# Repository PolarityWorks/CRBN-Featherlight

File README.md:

# CRBN-Featherlight

<br />The CRBN Featherlight is licensed under a <a rel="license" href="http://creativecommons.org/licenses/by-nc-sa/4.0/">Creative Commons Attribution-NonCommercial-ShareAlike 4.0 International License</a>.

The PCB and case design may be freely reproduced, modified, and manufactured for personal use and may not be reproduced for public sale.

If you have built upon this work please contact us at polarity.works.1@gmail.com. We fully support those looking to make new things and will most likely support your project.

[Build Guide](https://drive.google.com/file/d/1sr51WLZUvYGmcUbsTRLLeZIsZQXj4blm/view)

[Kits are sold here](https://keygem.store/collections/keyboards/products/group-buy-featherlight-40-kit)

[QMK Firmware](https://config.qmk.fm/#/crbn/LAYOUT_crbn_1x2u)

[ZMK Firmware](https://github.com/zmkfirmware/zmk/tree/main)

This little 40% ortho punches well above its weight and its price tag. Tough enough to survive life on the go or beating down someone that disses it.
It's got all the configuration options you'd ever want in a 40%. All the components are through-hole so it's a great first keyboard kit to put togethether.
You will need a pro micro for the PCB which gives you lots of options for extra features. You can solder in an elite c to get USB C or even a nice nano to make it wireless! There's plenty of room between the PCB and the bottom plate for a huge lithium battery.
This would be a vicious travel keyboard, a macro pad for productivity people, the first ortho for people who want to try ortho, or just a cute little keyboard to lend to people when they need one.

## Specifications
* Only 300g
* Stacked carbon fiber switch plate and bottom
* Supoport for a rotary encoder - this can be place in one of the corners
* Sevral bottom row layouts
* QMK and ZMK support

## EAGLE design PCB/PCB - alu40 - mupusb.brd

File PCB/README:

Components Needed:
1N4148 DO-35 Diodes               x48
6x6mm tactile button              x1
12x1 pin header 2.54mm pitch      x2
Pro Micro Compatible or Nice Nano x1
Key Switches                      x44-48

Optional:
EC11 Rotary Encoder               x1
Stabilisers (2u or 4u)            x1-2

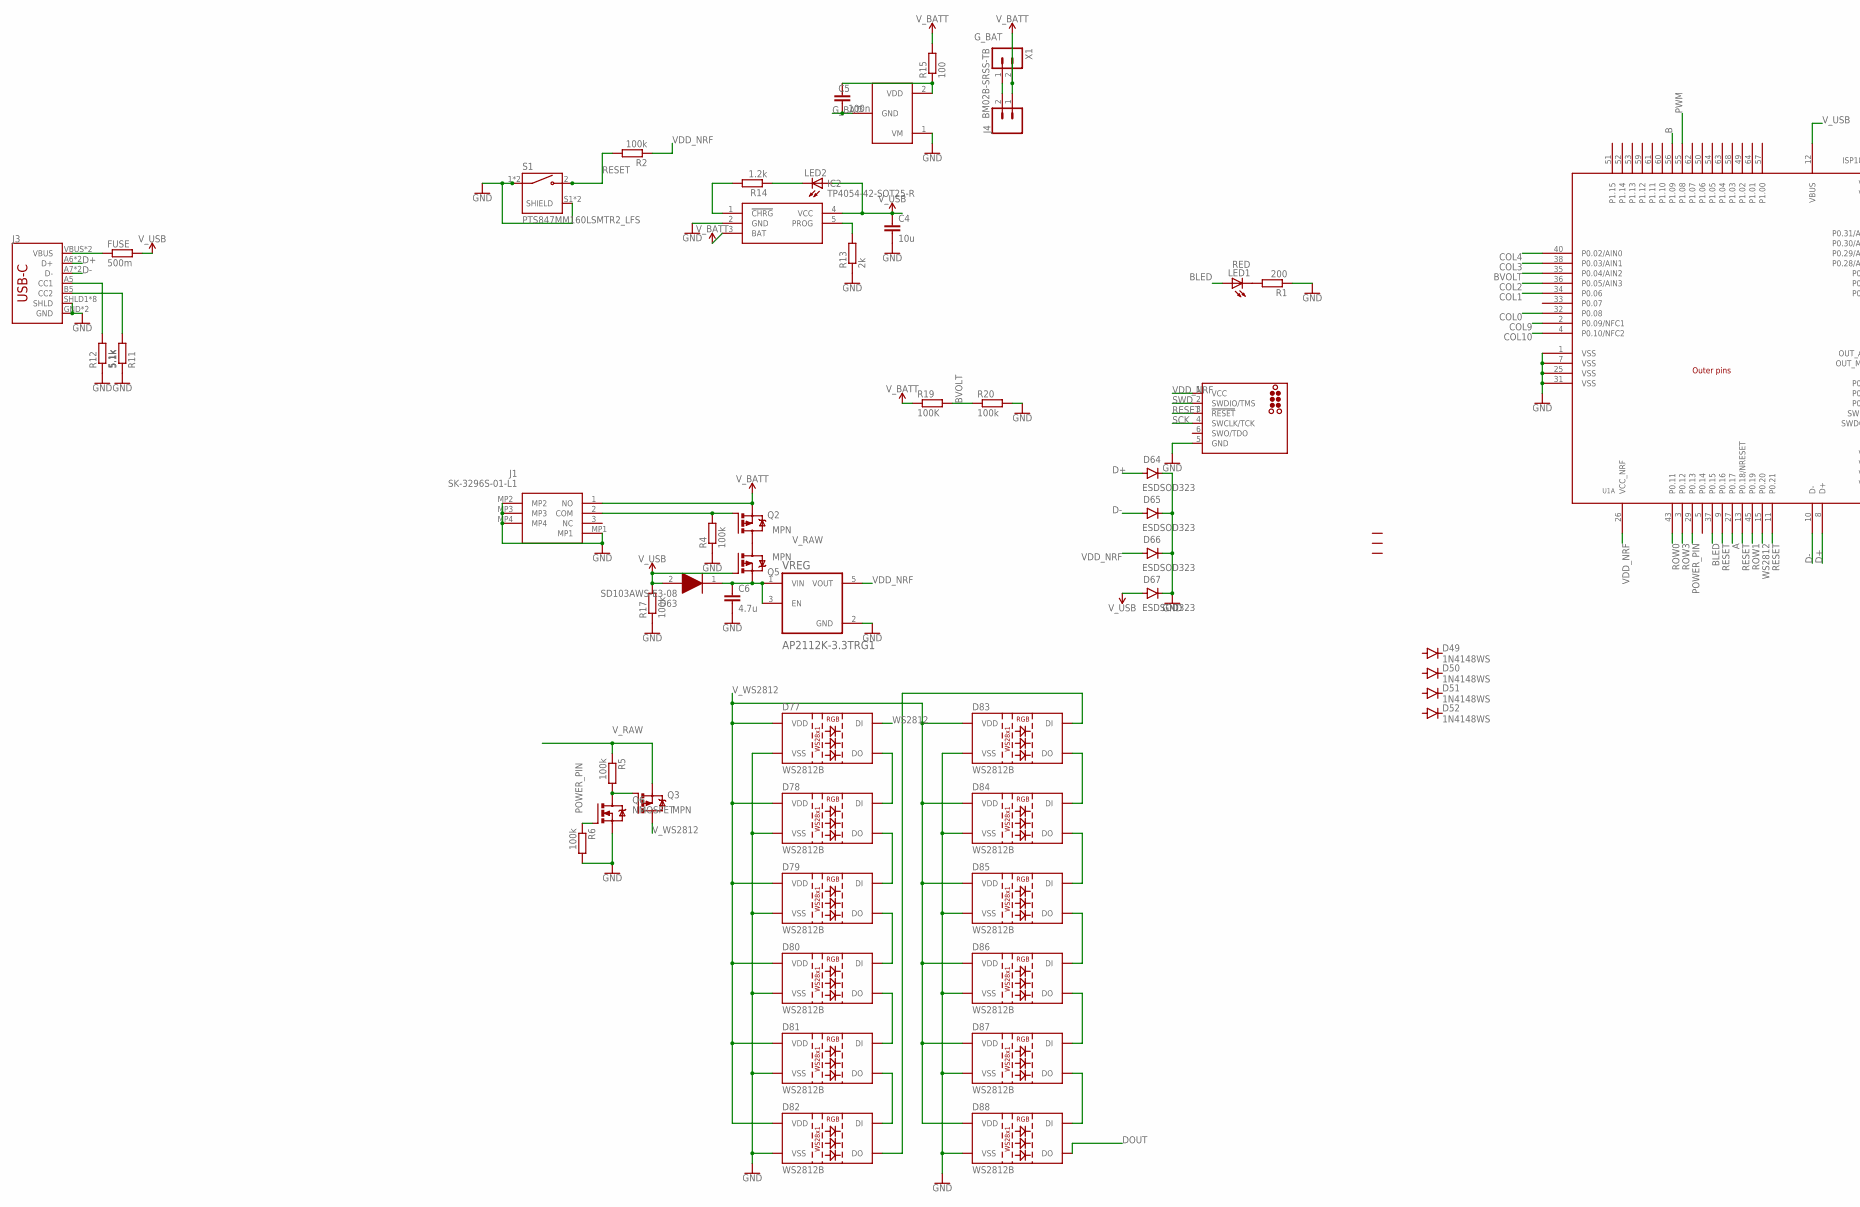
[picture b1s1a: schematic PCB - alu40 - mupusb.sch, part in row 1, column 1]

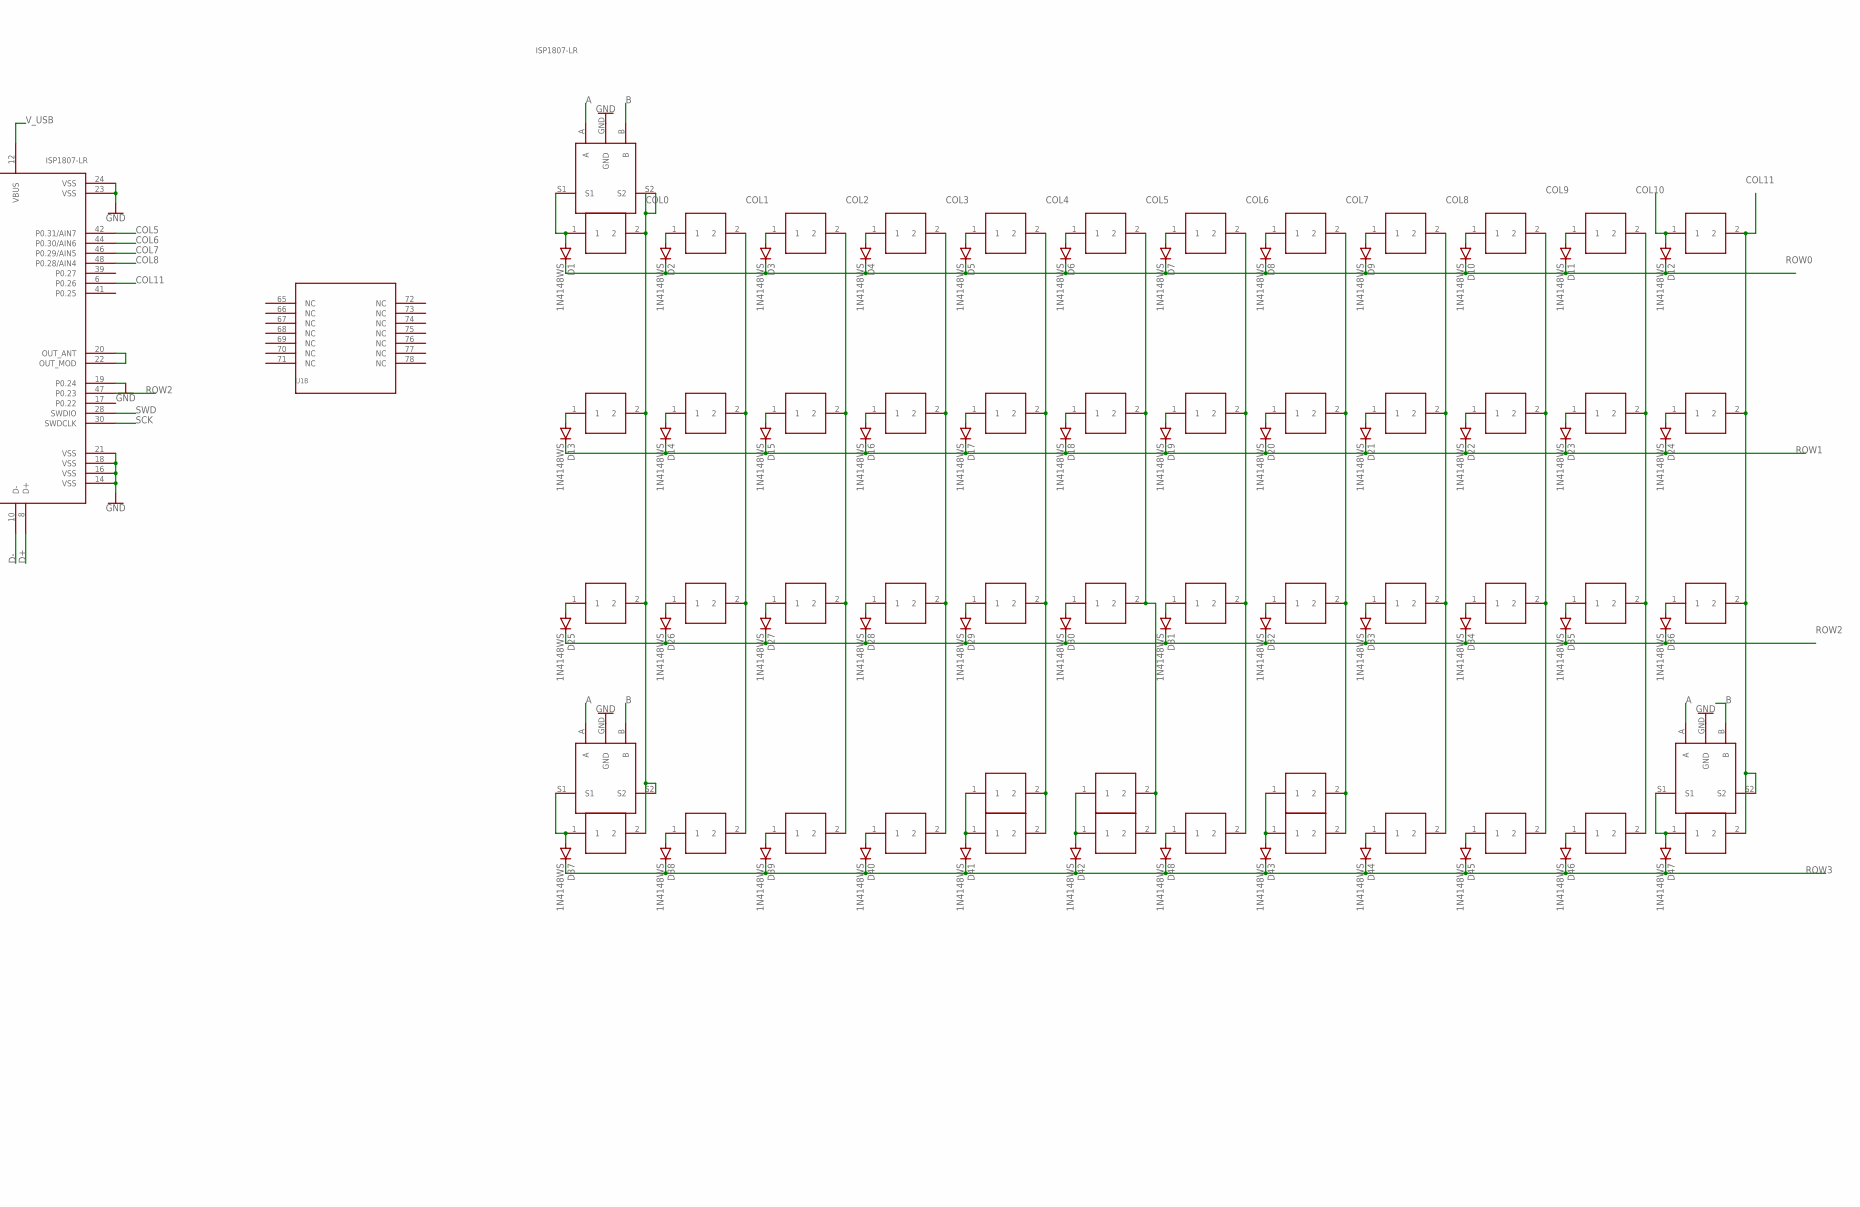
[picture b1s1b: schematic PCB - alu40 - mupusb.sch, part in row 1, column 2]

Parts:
11, 12, 13, 14, 15, 16, 17, 18, 19, 21, 22, 23, 24, 25, 26, 27, 28, 29, 31, 32, 33, 34, 35, 36, 37, 38, 39, 41, 42, 43, 44, 45, 45-2, 46, 46-2, 47, 48, 48-2, 49, 110, 111, 112, 210, 211, 212, 310, 311, 312, 410, 411, 412: CHERRY
11ENC, 41ENC\, 412ENC: ENCODERHOLE; ENCODER
C4: 10u; C0603
C5: 100n; C0603
C6: 4.7u; C0603
D1, D2, D3, D4, D5, D6, D7, D8, D9, D10, D11, D12, D13, D14, D15, D16, D17, D18, D19, D20, D21, D22, D23, D24, D25, D26, D27, D28, D29, D30, D31, D32, D33, D34, D35, D36, D37, D38, D39, D40, D41, D42, D43, D44, D45, D46, D47, D48, D49, D50, D51, D52: 1N4148WS; SOD-323
D63: SD103AWS-E3-08; SOD2713X115N
D64, D65, D66, D67: ESDSOD323; SOD-323
D77, D78, D79, D80, D81, D82, D83, D84, D85, D86, D87, D88: WS2812B
FUSE: 500m; R0603
IC1: XB3303ASOT23; SOT23-3
IC2: TP4054-42-SOT25-R; SOT95P280X100-5N
J1: SK-3296S-01-L1; SK3296S01L1
J2: TC2030_SWD-MCP-NL; TC2030-MCP-NL
J3: SPARKFUN-CONNECTORS_USB_C; MUP-MIDMNT-SS
J4: CONN_02; 1X02
LED1: RED; CHIPLED_0805
LED2: LEDCHIPLED_0805; CHIPLED_0805
Q2, Q3, Q5: PMOSFET; SOT23; MPN SL2301S
Q6: NMOSFET; SOT23
R1: 200; R0603
R2, R4, R5, R6, R17, R20: 100k; R0603
R11, R12: 5.1k; R0603
R13: 2k; R0603
R14: 1.2k; R0603
R15: 100; R0603
R19: 100K; R0603
S1: PTS847MM160LSMTR2_LFS; SW_PTS847MM160LSMTR2_LFS
U1: ISP1807-LRISP1807-LR_ISP1807-LR; ISP1807-LR
U$8, U$9, U$10: STAB-2U
VREG: AP2112K-3.3TRG1; SOT95P285X140-5N
X1: BM02B-SRSS-TB

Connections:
A: 11ENC.A, 41ENC\.A, 412ENC.A, U1.27 (P0.17)
B: 11ENC.B, 41ENC\.B, 412ENC.B, U1.56 (P1.09)
BLED: LED1.A, U1.37 (P0.15)
BVOLT: R19.2, R20.1, U1.35 (P0.04/AIN2)
COL0: 11.2, 11ENC.S2, 21.2, 31.2, 41.2, 41ENC\.S2, U1.32 (P0.08)
COL1: 12.2, 22.2, 32.2, 42.2, U1.34 (P0.06)
COL2: 13.2, 23.2, 33.2, 43.2, U1.36 (P0.05/AIN3)
COL3: 14.2, 24.2, 34.2, 44.2, U1.38 (P0.03/AIN1)
COL4: 15.2, 25.2, 35.2, 45.2, 45-2.2, U1.40 (P0.02/AIN0)
COL5: 16.2, 26.2, 36.2, 46.2, 46-2.2, U1.42 (P0.31/AIN7)
COL6: 17.2, 27.2, 37.2, 47.2, U1.44 (P0.30/AIN6)
COL7: 18.2, 28.2, 38.2, 48.2, 48-2.2, U1.46 (P0.29/AIN5)
COL8: 19.2, 29.2, 39.2, 49.2, U1.48 (P0.28/AIN4)
COL9: 110.2, 210.2, 310.2, 410.2, U1.2 (P0.09/NFC1)
COL10: 111.2, 211.2, 311.2, 411.2, U1.4 (P0.10/NFC2)
COL11: 112.2, 212.2, 312.2, 412.2, 412ENC.S2, U1.6 (P0.26)
D+: D64.A, J3.A6 (D+), J3.B6 (D+), U1.8 (D+)
D-: D65.A, J3.A7 (D-), J3.B7 (D-), U1.10 (D-)
DOUT: D88.2 (DO)
GND: 11ENC.GND, 41ENC\.GND, 412ENC.GND, C4.2, C6.2, D64.C, D65.C, D66.C, D67.C, D77.3 (VSS), D78.3 (VSS), D79.3 (VSS), D80.3 (VSS), D81.3 (VSS), D82.3 (VSS), D83.3 (VSS), D84.3 (VSS), D85.3 (VSS), D86.3 (VSS), D87.3 (VSS), D88.3 (VSS), IC1.1 (VM), IC2.2 (GND), J1.MP1, J1.MP2, J1.MP3, J1.MP4, J2.5 (GND), J3.GND, J3.GND2 (GND), J3.SHLD1 (SHLD), J3.SHLD2 (SHLD), J3.SHLD3 (SHLD), J3.SHLD4 (SHLD), J3.SHLD5 (SHLD), J3.SHLD6 (SHLD), J3.SHLD7 (SHLD), J3.SHLD8 (SHLD), Q6.2 (S), R1.1, R4.1, R6.2, R11.1, R12.1, R13.1, R17.1, R20.2, S1.1 (COM), S1.3 (COM), S1.S1 (SHIELD), S1.S2 (SHIELD), U1.1 (VSS), U1.7 (VSS), U1.14 (VSS), U1.16 (VSS), U1.18 (VSS), U1.19 (P0.24), U1.21 (VSS), U1.23 (VSS), U1.24 (VSS), U1.25 (VSS), U1.31 (VSS), VREG.2 (GND)
G_BAT: C5.2, IC1.3 (GND), J4.2, X1.1
unnamed: 47.1, D48.A
unnamed: 12.1, D2.A
unnamed: 13.1, D3.A
unnamed: 14.1, D4.A
unnamed: 15.1, D5.A
unnamed: 16.1, D6.A
unnamed: 17.1, D7.A
unnamed: 18.1, D8.A
unnamed: 19.1, D9.A
unnamed: 110.1, D10.A
unnamed: 111.1, D11.A
unnamed: 112.1, D12.A
unnamed: 21.1, D13.A
unnamed: 22.1, D14.A
unnamed: 23.1, D15.A
unnamed: 24.1, D16.A
unnamed: 25.1, D17.A
unnamed: 26.1, D18.A
unnamed: 27.1, D19.A
unnamed: 28.1, D20.A
unnamed: 29.1, D21.A
unnamed: 210.1, D22.A
unnamed: 211.1, D23.A
unnamed: 212.1, D24.A
unnamed: 31.1, D25.A
unnamed: 32.1, D26.A
unnamed: 33.1, D27.A
unnamed: 34.1, D28.A
unnamed: 35.1, D29.A
unnamed: 36.1, D30.A
unnamed: 37.1, D31.A
unnamed: 38.1, D32.A
unnamed: 39.1, D33.A
unnamed: 310.1, D34.A
unnamed: 311.1, D35.A
unnamed: 312.1, D36.A
unnamed: D77.2 (DO), D78.4 (DI)
unnamed: 42.1, D38.A
unnamed: 43.1, D39.A
unnamed: 44.1, D40.A
unnamed: 45.1, 45-2.1, D41.A
unnamed: U1.20 (OUT_ANT), U1.22 (OUT_MOD)
unnamed: 48.1, 48-2.1, D43.A
unnamed: 49.1, D44.A
unnamed: 410.1, D45.A
unnamed: 411.1, D46.A
unnamed: 46.1, 46-2.1, D42.A
unnamed: 412.1, 412ENC.S1, D47.A
unnamed: 41.1, 41ENC\.S1, D37.A
unnamed: LED1.C, R1.2
unnamed: C5.1, IC1.2 (VDD), R15.1
unnamed: IC2.5 (PROG), R13.2
unnamed: J3.A5 (CC1), R12.2
unnamed: J3.B5 (CC2), R11.2
unnamed: IC2.1 (!CHRG), R14.2
unnamed: LED2.C, R14.1
unnamed: Q2.3 (D), Q5.3 (D)
unnamed: FUSE.1, J3.VBUS, J3.VBUS2 (VBUS)
unnamed: 11.1, 11ENC.S1, D1.A
unnamed: J1.2 (COM), Q2.1 (G), R4.2
unnamed: Q3.1 (G), Q6.3 (D), R5.2
unnamed: D78.2 (DO), D79.4 (DI)
unnamed: D79.2 (DO), D80.4 (DI)
unnamed: D80.2 (DO), D81.4 (DI)
unnamed: D81.2 (DO), D82.4 (DI)
unnamed: D82.2 (DO), D83.4 (DI)
unnamed: D83.2 (DO), D84.4 (DI)
unnamed: D84.2 (DO), D85.4 (DI)
unnamed: D85.2 (DO), D86.4 (DI)
unnamed: D86.2 (DO), D87.4 (DI)
unnamed: D87.2 (DO), D88.4 (DI)
POWER_PIN: Q6.1 (G), R6.1, U1.29 (P0.13)
PWM: U1.55 (P1.08)
RESET: J2.3 (!RESET), R2.2, S1.2 (NO), U1.9 (P0.16), U1.11 (P0.21), U1.13 (P0.18/NRESET)
ROW0: D1.C, D2.C, D3.C, D4.C, D5.C, D6.C, D7.C, D8.C, D9.C, D10.C, D11.C, D12.C, U1.43 (P0.11)
ROW1: D13.C, D14.C, D15.C, D16.C, D17.C, D18.C, D19.C, D20.C, D21.C, D22.C, D23.C, D24.C, U1.45 (P0.19)
ROW2: D25.C, D26.C, D27.C, D28.C, D29.C, D30.C, D31.C, D32.C, D33.C, D34.C, D35.C, D36.C, U1.47 (P0.23)
ROW3: D37.C, D38.C, D39.C, D40.C, D41.C, D42.C, D43.C, D44.C, D45.C, D46.C, D47.C, D48.C, U1.3 (P0.12)
SCK: J2.4 (SWCLK/TCK), U1.30 (SWDCLK)
SWD: J2.2 (SWDIO/TMS), U1.28 (SWDIO)
VDD_NRF: D66.A, J2.1 (VCC), R2.1, U1.26 (VCC_NRF), VREG.5 (VOUT)
V_BATT: IC2.3 (BAT), J1.1 (NO), J4.1, Q2.2 (S), R15.2, R19.1, X1.2
V_RAW: C6.1, D63.1 (K), Q3.2 (S), Q5.2 (S), R5.1, VREG.1 (VIN), VREG.3 (EN)
V_USB: C4.1, D63.2 (A), D67.A, FUSE.2, IC2.4 (VCC), LED2.A, Q5.1 (G), R17.2, U1.12 (VBUS)
V_WS2812: D77.1 (VDD), D78.1 (VDD), D79.1 (VDD), D80.1 (VDD), D81.1 (VDD), D82.1 (VDD), D83.1 (VDD), D84.1 (VDD), D85.1 (VDD), D86.1 (VDD), D87.1 (VDD), D88.1 (VDD), Q3.3 (D)
WS2812: D77.4 (DI), U1.15 (P0.20)

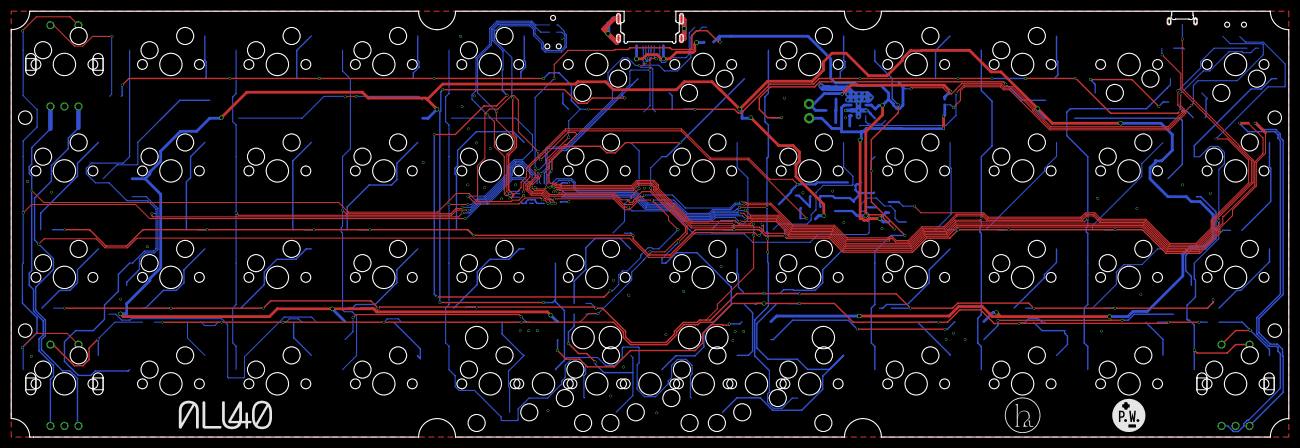
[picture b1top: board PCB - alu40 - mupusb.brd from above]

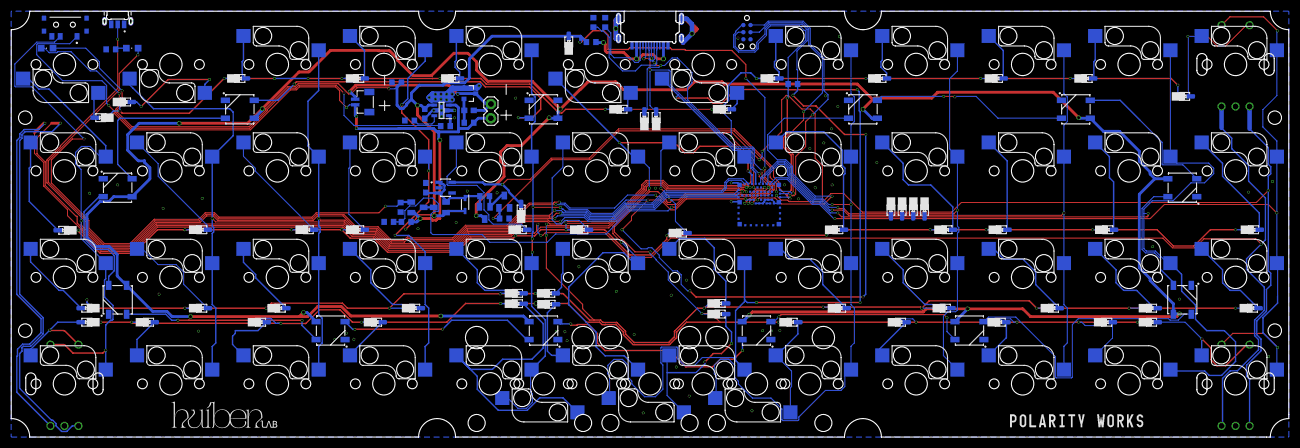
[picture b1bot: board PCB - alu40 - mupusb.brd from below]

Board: 2 copper layers, 228.0 x 76.0 mm, 159 parts (102 on the bottom side), 105 nets.

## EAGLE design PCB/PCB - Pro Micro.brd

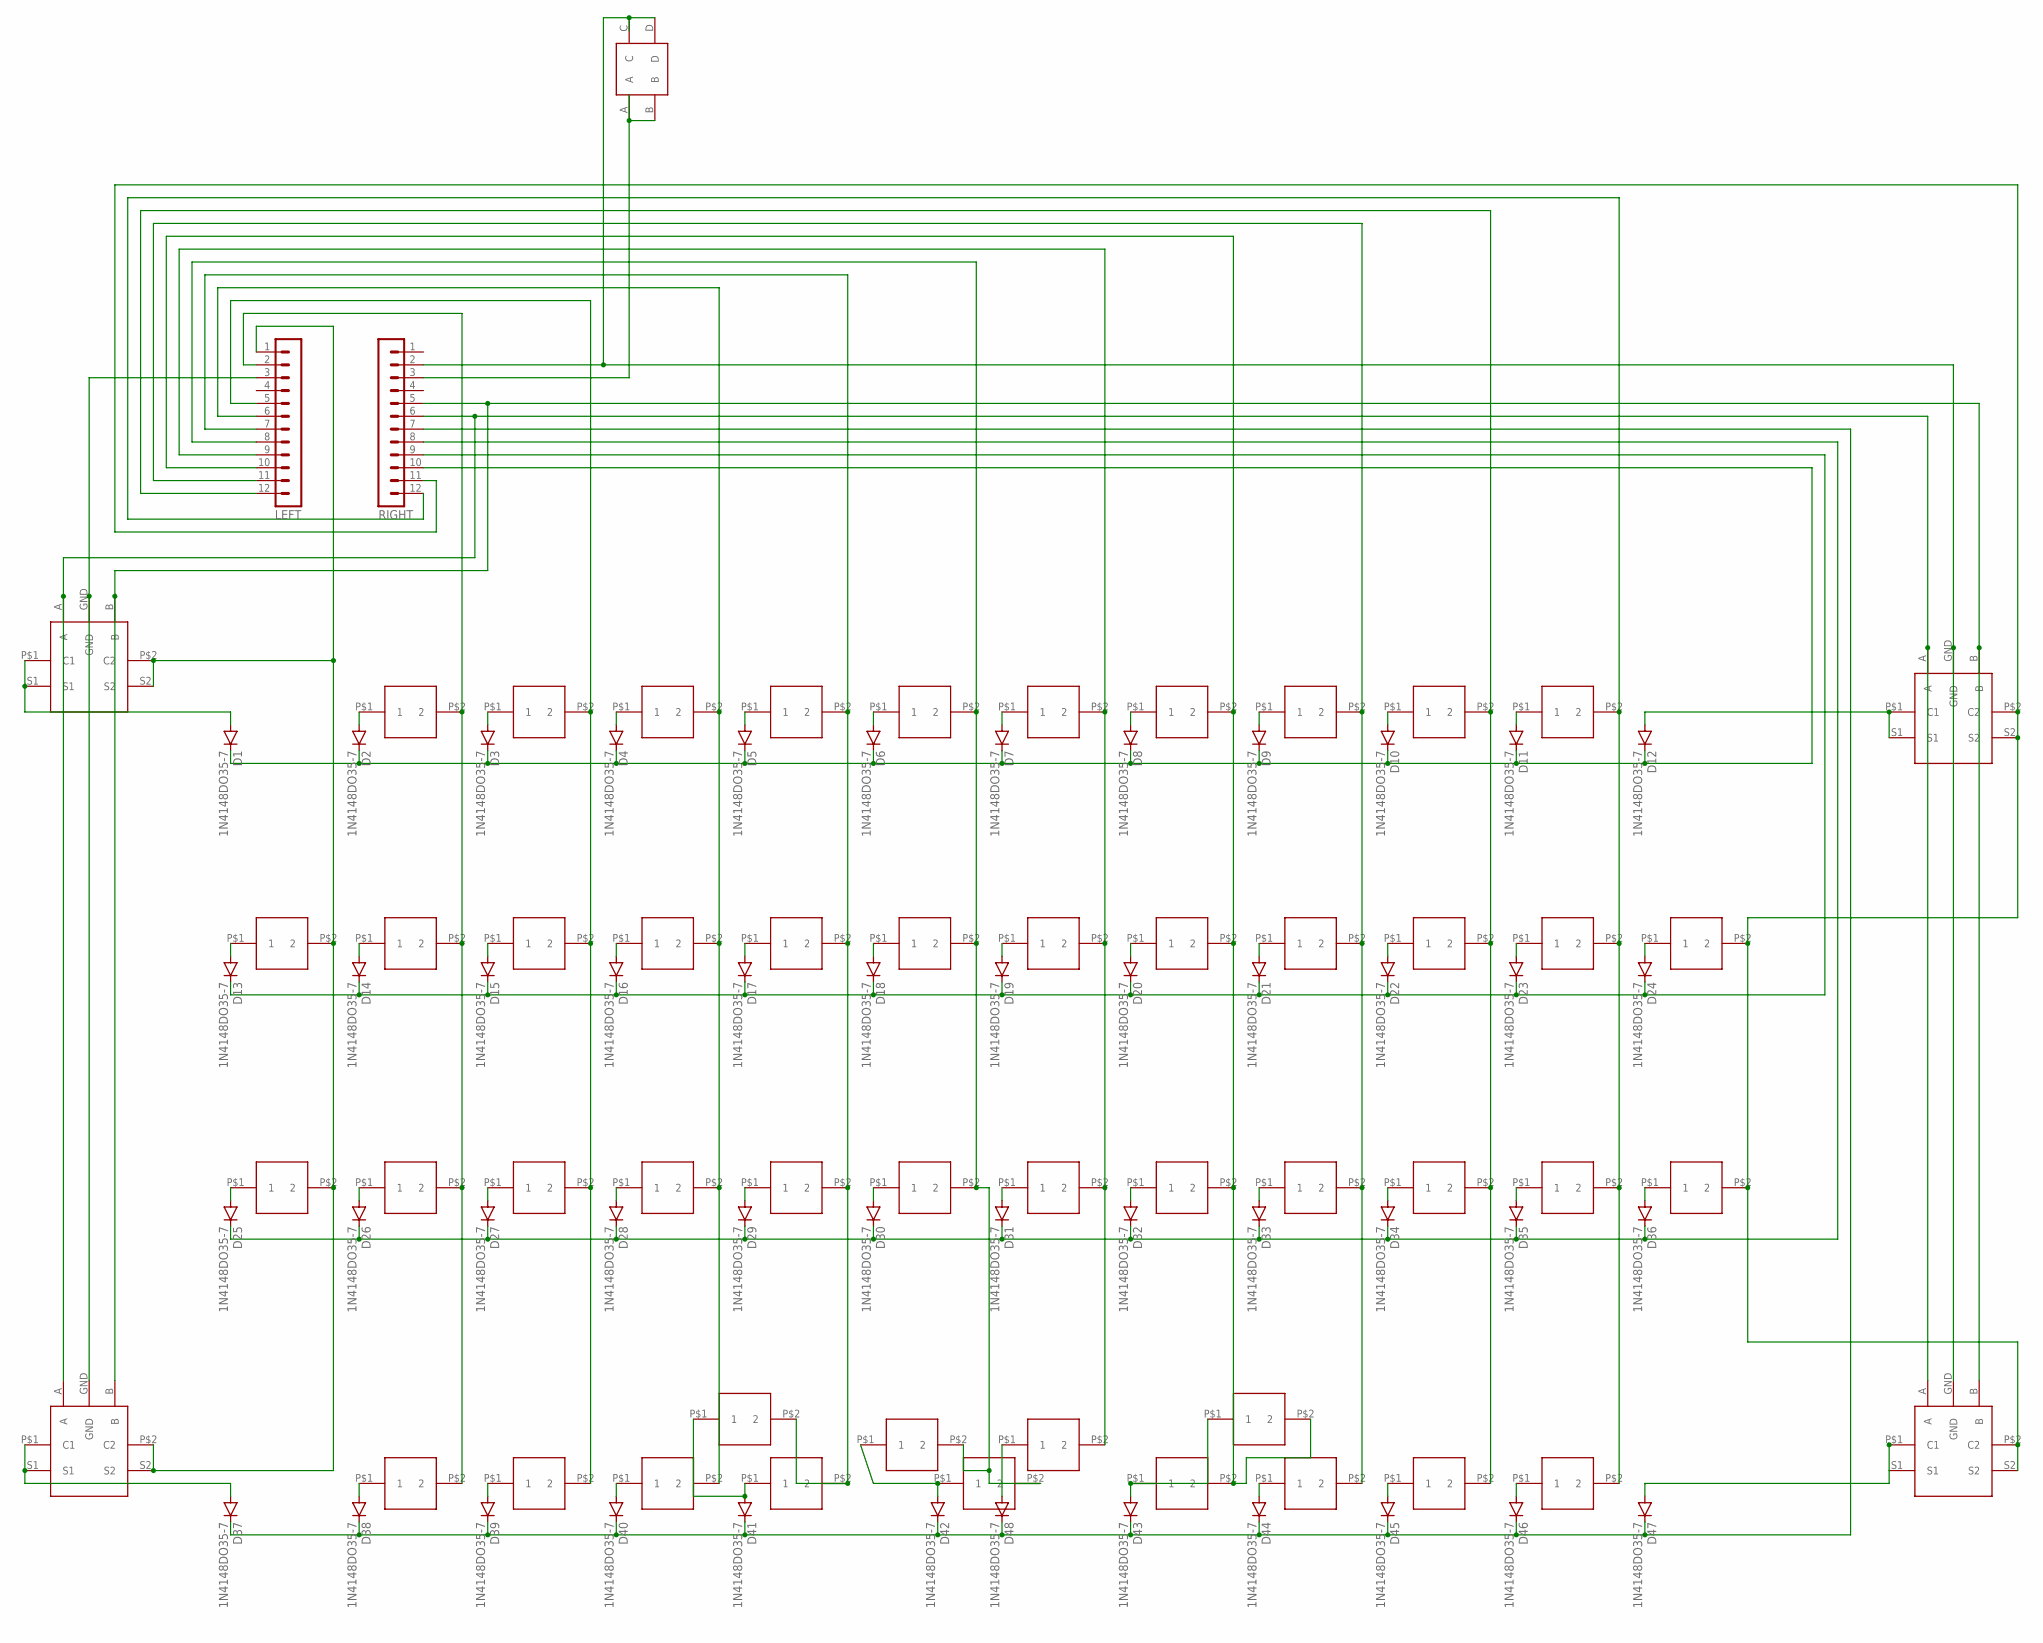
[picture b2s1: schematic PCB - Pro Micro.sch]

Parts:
1, 2, 3, 4, 12, 13, 14, 15, 16, 17, 18, 19, 21, 22, 23, 24, 25, 26, 27, 28, 29, 31, 32, 33, 34, 35, 36, 37, 38, 39, 42, 43, 44, 45, 46, 47, 48, 49, 110, 111, 210, 211, 212, 310, 311, 312, 410: CHERRY-SOLDER
D1, D2, D3, D4, D5, D6, D7, D8, D9, D10, D11, D12, D13, D14, D15, D16, D17, D18, D19, D20, D21, D22, D23, D24, D25, D26, D27, D28, D29, D30, D31, D32, D33, D34, D35, D36, D37, D38, D39, D40, D41, D42, D43, D44, D45, D46, D47, D48: 1N4148DO35-7; DO35-7
LEFT: MA12-1
RIGHT: MA12-1
U$1: BUTTON
U$2, U$3, U$4, U$5: CHERRY-ENCODER

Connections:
unnamed: 3.P$2 (2), 15.P$2 (2), 25.P$2 (2), 35.P$2 (2), 45.P$2 (2), LEFT.7
unnamed: 12.P$1 (1), D2.A
unnamed: 13.P$1 (1), D3.A
unnamed: 14.P$1 (1), D4.A
unnamed: 15.P$1 (1), D5.A
unnamed: 16.P$1 (1), D6.A
unnamed: 17.P$1 (1), D7.A
unnamed: 18.P$1 (1), D8.A
unnamed: 19.P$1 (1), D9.A
unnamed: 110.P$1 (1), D10.A
unnamed: 111.P$1 (1), D11.A
unnamed: D12.A, U$2.P$1 (C1), U$2.S1
unnamed: 21.P$1 (1), D13.A
unnamed: 22.P$1 (1), D14.A
unnamed: 23.P$1 (1), D15.A
unnamed: 24.P$1 (1), D16.A
unnamed: 25.P$1 (1), D17.A
unnamed: 26.P$1 (1), D18.A
unnamed: 27.P$1 (1), D19.A
unnamed: 28.P$1 (1), D20.A
unnamed: 29.P$1 (1), D21.A
unnamed: 210.P$1 (1), D22.A
unnamed: 211.P$1 (1), D23.A
unnamed: 212.P$1 (1), D24.A
unnamed: 31.P$1 (1), D25.A
unnamed: 32.P$1 (1), D26.A
unnamed: 33.P$1 (1), D27.A
unnamed: 34.P$1 (1), D28.A
unnamed: 35.P$1 (1), D29.A
unnamed: 36.P$1 (1), D30.A
unnamed: 37.P$1 (1), D31.A
unnamed: 38.P$1 (1), D32.A
unnamed: 39.P$1 (1), D33.A
unnamed: 310.P$1 (1), D34.A
unnamed: 311.P$1 (1), D35.A
unnamed: 312.P$1 (1), D36.A
unnamed: 21.P$2 (2), 31.P$2 (2), LEFT.1, U$3.P$2 (C2), U$3.S2, U$4.P$2 (C2), U$4.S2
unnamed: 42.P$1 (1), D38.A
unnamed: 43.P$1 (1), D39.A
unnamed: 44.P$1 (1), D40.A
unnamed: 3.P$1 (1), 45.P$1 (1), D41.A
unnamed: 1.P$1 (1), 46.P$1 (1), D42.A
unnamed: 4.P$1 (1), 47.P$1 (1), D43.A
unnamed: 48.P$1 (1), D44.A
unnamed: 49.P$1 (1), D45.A
unnamed: 410.P$1 (1), D46.A
unnamed: D47.A, U$5.P$1 (C1), U$5.S1
unnamed: D37.A, U$4.P$1 (C1), U$4.S1
unnamed: 212.P$2 (2), 312.P$2 (2), RIGHT.11, U$2.P$2 (C2), U$2.S2, U$5.P$2 (C2), U$5.S2
unnamed: 12.P$2 (2), 22.P$2 (2), 32.P$2 (2), 42.P$2 (2), LEFT.2
unnamed: D37.C, D38.C, D39.C, D40.C, D41.C, D42.C, D43.C, D44.C, D45.C, D46.C, D47.C, D48.C, RIGHT.7
unnamed: D1.C, D2.C, D3.C, D4.C, D5.C, D6.C, D7.C, D8.C, D9.C, D10.C, D11.C, D12.C, RIGHT.10
unnamed: D13.C, D14.C, D15.C, D16.C, D17.C, D18.C, D19.C, D20.C, D21.C, D22.C, D23.C, D24.C, RIGHT.9
unnamed: D25.C, D26.C, D27.C, D28.C, D29.C, D30.C, D31.C, D32.C, D33.C, D34.C, D35.C, D36.C, RIGHT.8
unnamed: RIGHT.2, U$1.C, U$1.D, U$2.GND, U$5.GND
unnamed: LEFT.3, U$3.GND, U$4.GND
unnamed: 13.P$2 (2), 23.P$2 (2), 33.P$2 (2), 43.P$2 (2), LEFT.5
unnamed: 111.P$2 (2), 211.P$2 (2), 311.P$2 (2), 410.P$2 (2), RIGHT.12
unnamed: RIGHT.6, U$2.A, U$3.A, U$4.A, U$5.A
unnamed: D1.A, U$3.P$1 (C1), U$3.S1
unnamed: 14.P$2 (2), 24.P$2 (2), 34.P$2 (2), 44.P$2 (2), LEFT.6
unnamed: RIGHT.5, U$2.B, U$3.B, U$4.B, U$5.B
unnamed: 2.P$1 (1), D48.A
unnamed: 2.P$2 (2), 17.P$2 (2), 27.P$2 (2), 37.P$2 (2), LEFT.9
unnamed: 49.P$2 (2), 110.P$2 (2), 210.P$2 (2), 310.P$2 (2), LEFT.12
unnamed: 1.P$2 (2), 16.P$2 (2), 26.P$2 (2), 36.P$2 (2), 46.P$2 (2), LEFT.8
unnamed: RIGHT.3, U$1.A, U$1.B
unnamed: 4.P$2 (2), 18.P$2 (2), 28.P$2 (2), 38.P$2 (2), 47.P$2 (2), LEFT.10
unnamed: 19.P$2 (2), 29.P$2 (2), 39.P$2 (2), 48.P$2 (2), LEFT.11

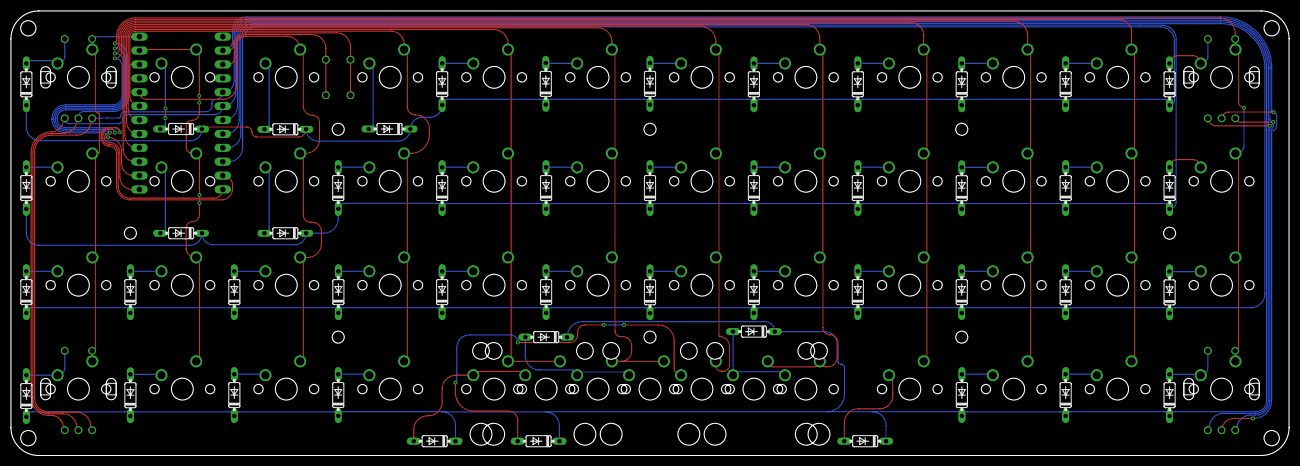
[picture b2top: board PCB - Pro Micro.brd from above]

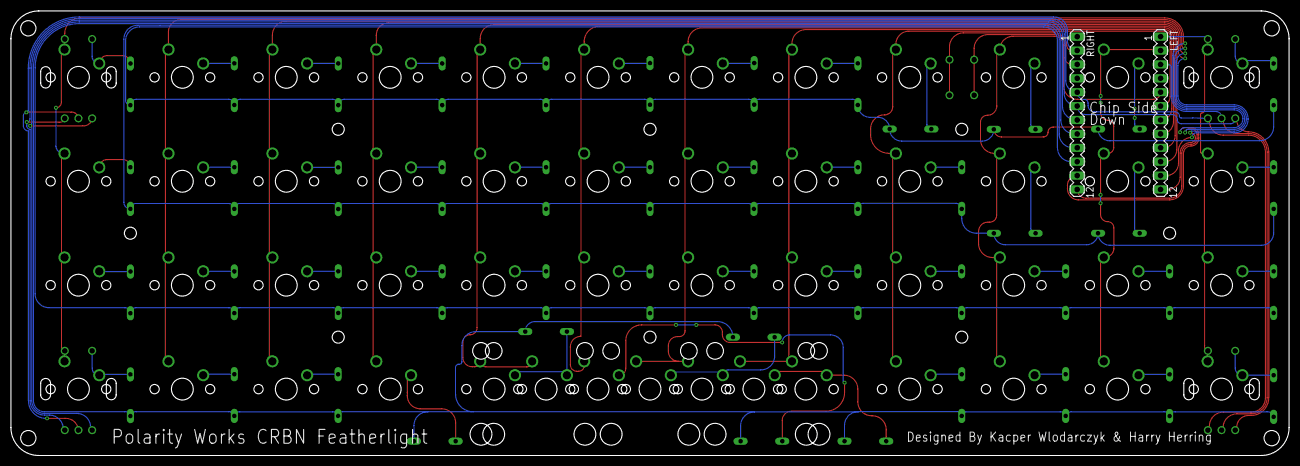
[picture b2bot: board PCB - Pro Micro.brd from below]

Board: 2 copper layers, 233.7 x 81.3 mm, 102 parts (2 on the bottom side), 69 nets.

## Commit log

2021-01-09 Create LICENSE
2021-01-09 Create ol
2021-01-09 Create f
2021-01-09 Update and rename f to README
2021-12-04 new pcb push
2021-12-27 add vias
2021-12-30 DRC fixes and GERBERs
2022-10-17 alu40 cimmut
2022-10-17 Moved connector - added silk
2022-10-17 Updated connector position
2022-10-17 Final connector update
2022-10-17 GERBERS
2022-10-21 Add standoffs
2022-10-21 Add Bcream
2022-10-21 GERBER
2022-12-11 Move reset switch
2023-02-04 Remove unnecessary swd pin
2023-03-04 Add Via
2023-03-13 add silk, spare diodes, move D1
2023-03-13 Add lgoos to unused layer
2023-03-16 logo position update
2023-03-20 Change component vals
2023-06-01 New usb prototyps
2023-06-02 Generated GERBERs
2023-12-30 Add Tagconnect and thermal relif for tp4054
2024-06-02 most of new updates
    Needs new reset and power switch, new USB port
2024-06-03 Route new switch footprints
2024-08-06 Commit gerbers
2024-08-06 tweak usb
2024-08-29 Move silk to custom layers
2024-10-31 Move LEDs across bottom
2024-11-01 Move top and bottom layer graphics

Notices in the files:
parts and their libraries:
SparkFun-Connectors: Licensing: Creative Commons ShareAlike 4.0 International - https://creativecommons.org/licenses/by-sa/4.0
tag-connect: ©2009 ROFA.cz - modified and updated by Robert Darlington ‹rdarlington@gmail.com›
